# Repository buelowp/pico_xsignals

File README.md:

# MRR Crossing Signal Controls

Control common anode LED RR crossing signals using a Pi Pico

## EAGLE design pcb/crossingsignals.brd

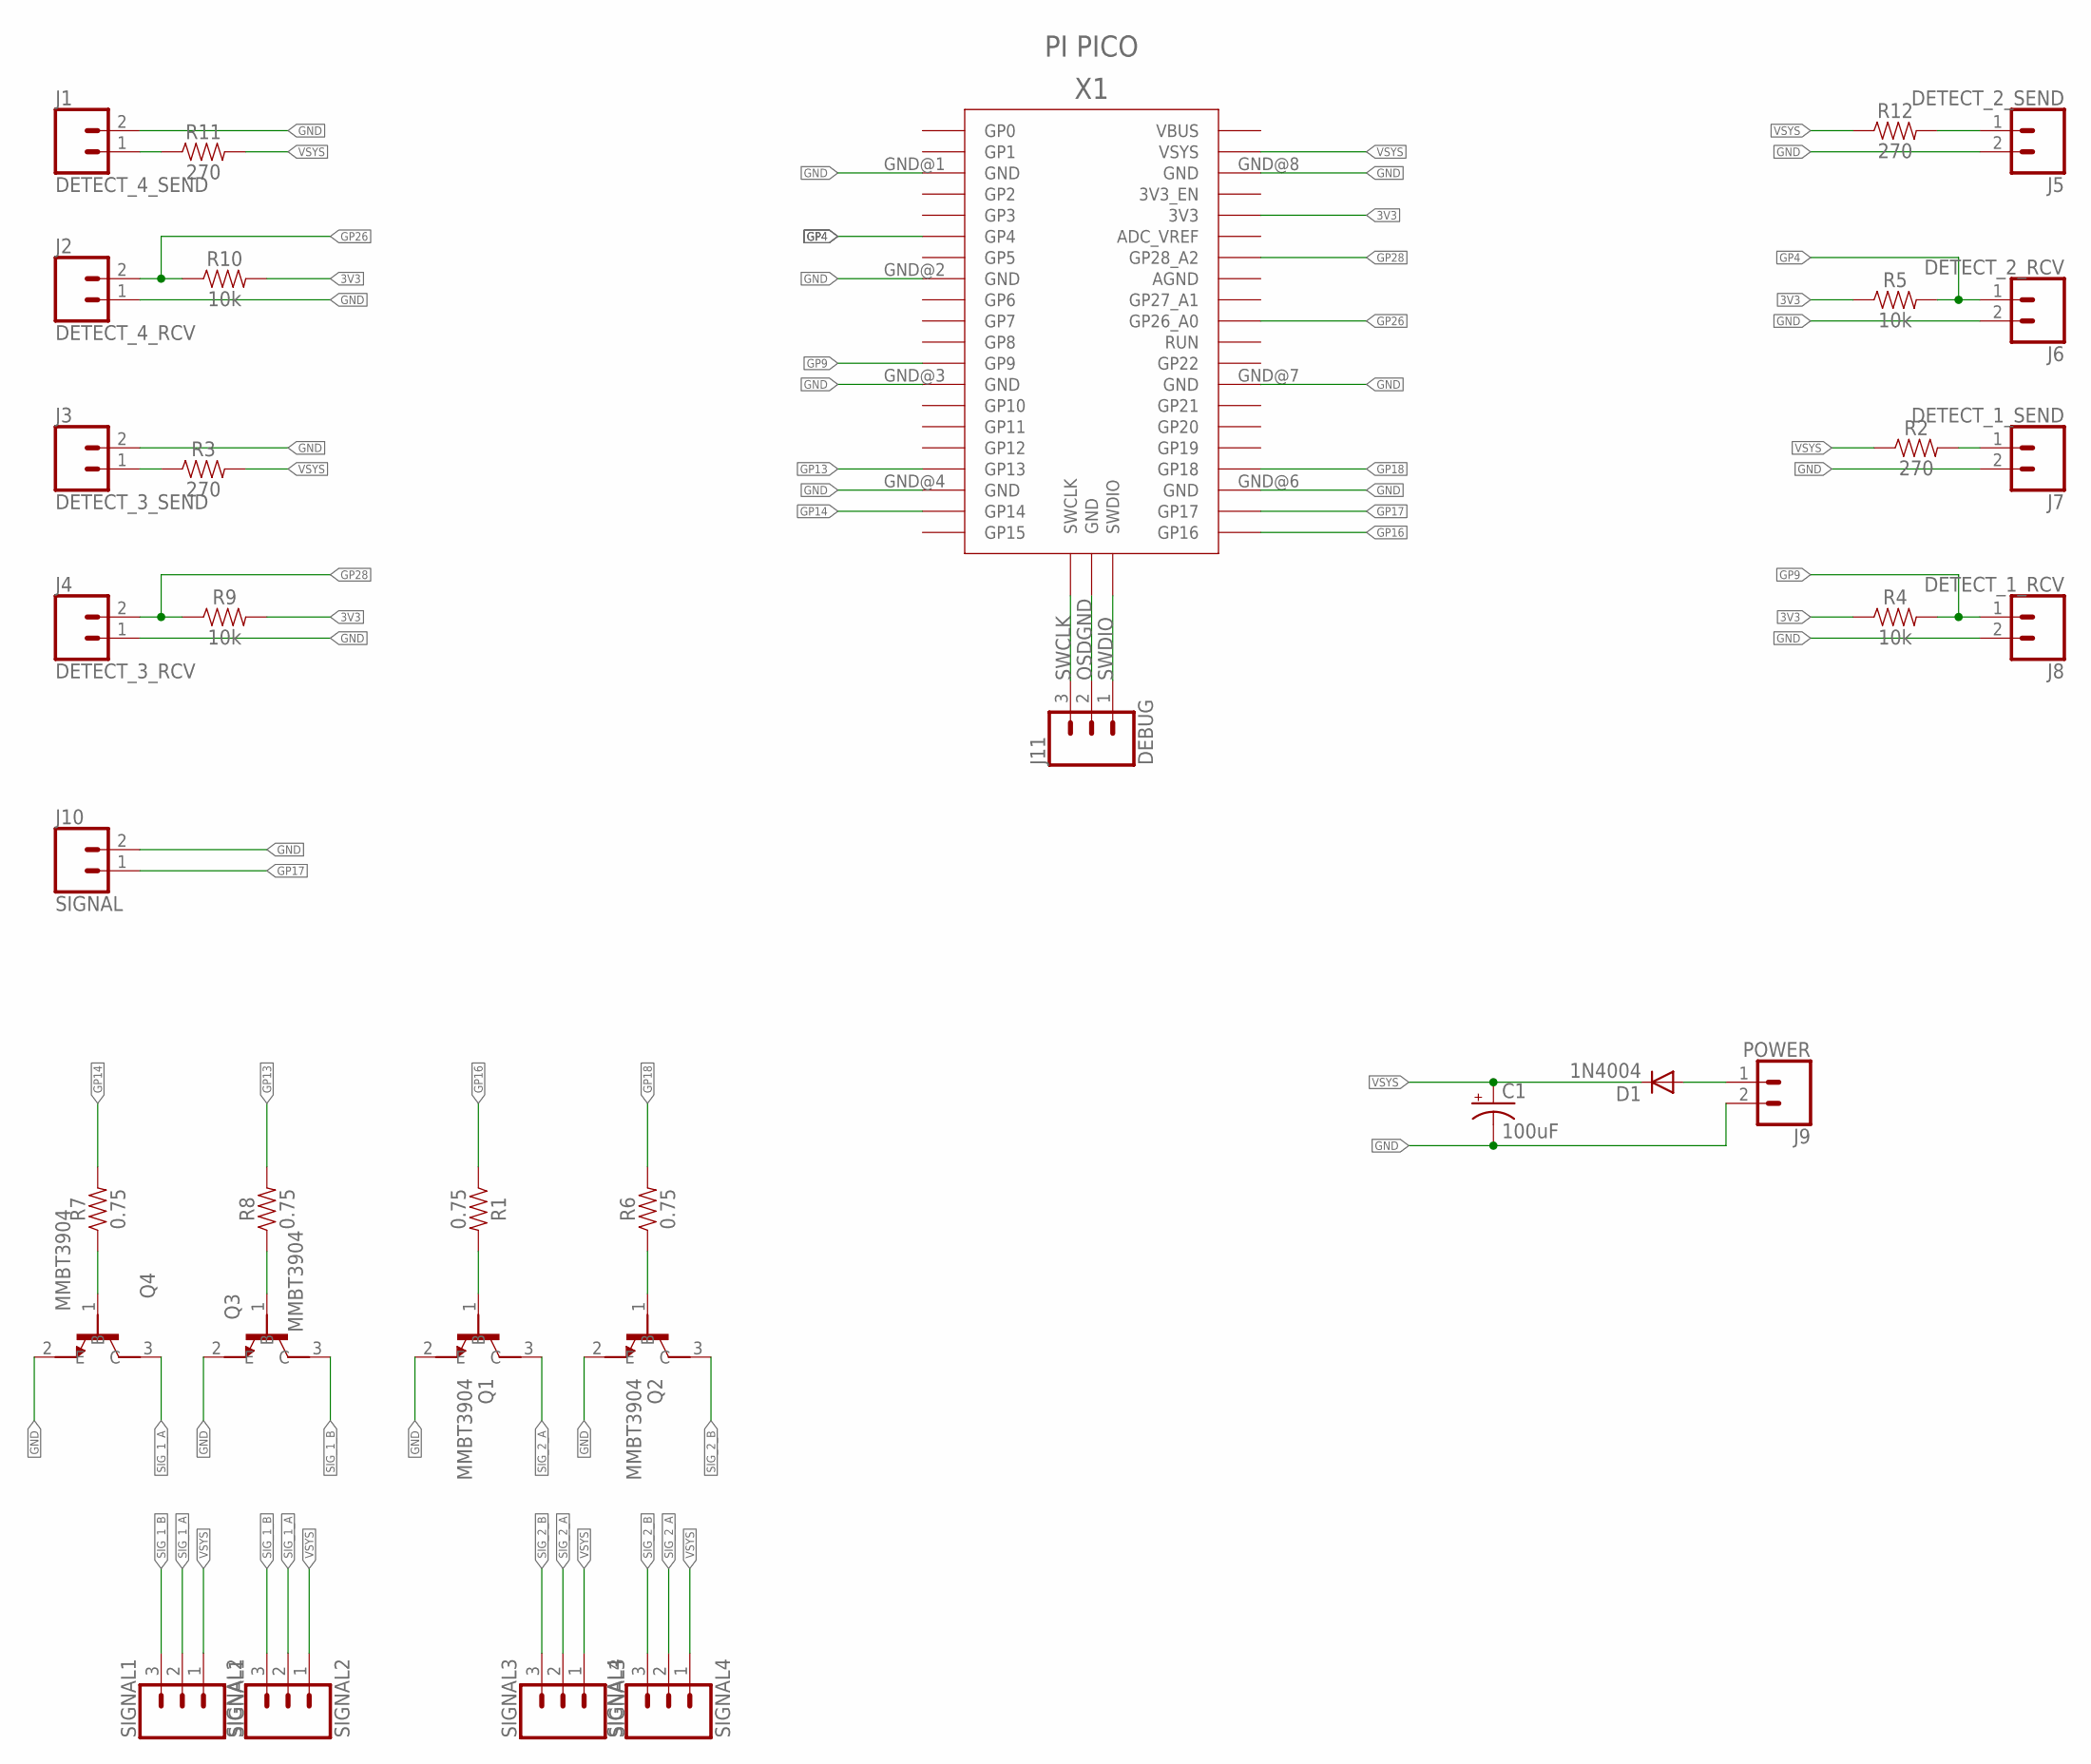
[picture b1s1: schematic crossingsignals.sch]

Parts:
C1: 100uF; CPOL-RADIAL-2.5MM-6.5MM
D1: 1N4004; DO41-10
J1: DETECT_4_SEND; 1X02
J2: DETECT_4_RCV; 1X02
J3: DETECT_3_SEND; 1X02
J4: DETECT_3_RCV; 1X02
J5: DETECT_2_SEND; 1X02
J6: DETECT_2_RCV; 1X02
J7: DETECT_1_SEND; 1X02
J8: DETECT_1_RCV; 1X02
J9: POWER; 1X02
J10: SIGNAL; 1X02
J11: DEBUG; 1X03
Q1, Q2, Q3, Q4: MMBT3904; SOT95P240X120-3N
R1, R6, R7, R8: 0.75; 0805
R2, R3, R11, R12: 270; 0805
R4, R5, R9, R10: 10k; 0805
SIGNAL1: SIGNAL1; 1X03
SIGNAL2: SIGNAL2; 1X03
SIGNAL3: SIGNAL3; 1X03
SIGNAL4: SIGNAL4; 1X03
X1: PI PICO; RPI_PICO_TH

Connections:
3V3: R4.1, R5.1, R9.2, R10.2, X1.3V3
GND: C1.2 (-), J1.2, J2.1, J3.2, J4.1, J5.2, J6.2, J7.2, J8.2, J9.2, J10.2, Q1.2 (E), Q2.2 (E), Q3.2 (E), Q4.2 (E), X1.GND@1 (GND), X1.GND@2 (GND), X1.GND@3 (GND), X1.GND@4 (GND), X1.GND@6 (GND), X1.GND@7 (GND), X1.GND@8 (GND)
GP4: J6.1, R5.2, X1.GP4
GP9: J8.1, R4.2, X1.GP9
GP13: R8.2, X1.GP13
GP14: R7.2, X1.GP14
GP16: R1.1, X1.GP16
GP17: J10.1, X1.GP17
GP18: R6.2, X1.GP18
GP26: J2.2, R10.1, X1.GP26_A0
GP28: J4.2, R9.1, X1.GP28_A2
unnamed: Q4.1 (B), R7.1
unnamed: Q3.1 (B), R8.1
unnamed: Q2.1 (B), R6.1
unnamed: D1.A, J9.1
unnamed: J3.1, R3.1
unnamed: J1.1, R11.1
unnamed: Q1.1 (B), R1.2
unnamed: J5.1, R12.2
unnamed: J7.1, R2.2
OSDGND: J11.2, X1.GND@5 (GND)
SIG_1_A: Q4.3 (C), SIGNAL1.2, SIGNAL2.2
SIG_1_B: Q3.3 (C), SIGNAL1.3, SIGNAL2.3
SIG_2_A: Q1.3 (C), SIGNAL3.2, SIGNAL4.2
SIG_2_B: Q2.3 (C), SIGNAL3.3, SIGNAL4.3
SWCLK: J11.3, X1.SWCLK
SWDIO: J11.1, X1.SWDIO
VSYS: C1.1 (+), D1.C, R2.1, R3.2, R11.2, R12.1, SIGNAL1.1, SIGNAL2.1, SIGNAL3.1, SIGNAL4.1, X1.VSYS

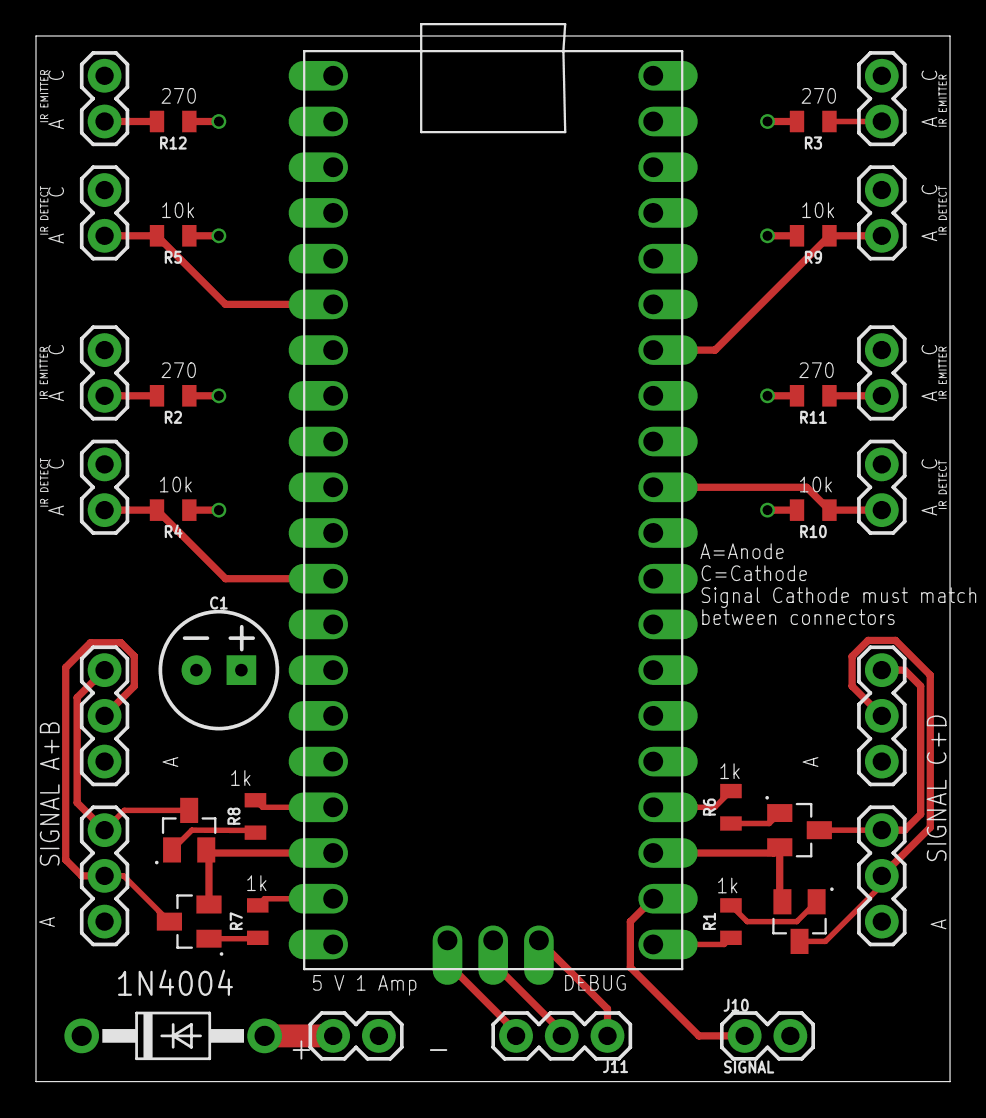
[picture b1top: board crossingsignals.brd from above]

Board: 4 copper layers, 50.8 x 58.1 mm, 34 parts (0 on the bottom side), 28 nets.

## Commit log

2021-02-22 Adding new content
2021-02-22 Adding PCB files
2021-02-22 Adding license header
2021-02-22 Fixing license header
2021-02-23 Add a turnoff function
    * Avoid leaving signals lit after a train exits.
    * Tell gitignore to ignore .vscode
2021-02-23 Adding a semaphore
    * Add a GPIO signal to act as a semaphore in case anyone wants to know
    when the signals are turned on or off
    * Fix the handling of the interrupts. It's not individual functions and
    should be smarter

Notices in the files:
parts and their libraries:
SparkFun-Connectors: Licensing: Creative Commons ShareAlike 4.0 International - https://creativecommons.org/licenses/by-sa/4.0
